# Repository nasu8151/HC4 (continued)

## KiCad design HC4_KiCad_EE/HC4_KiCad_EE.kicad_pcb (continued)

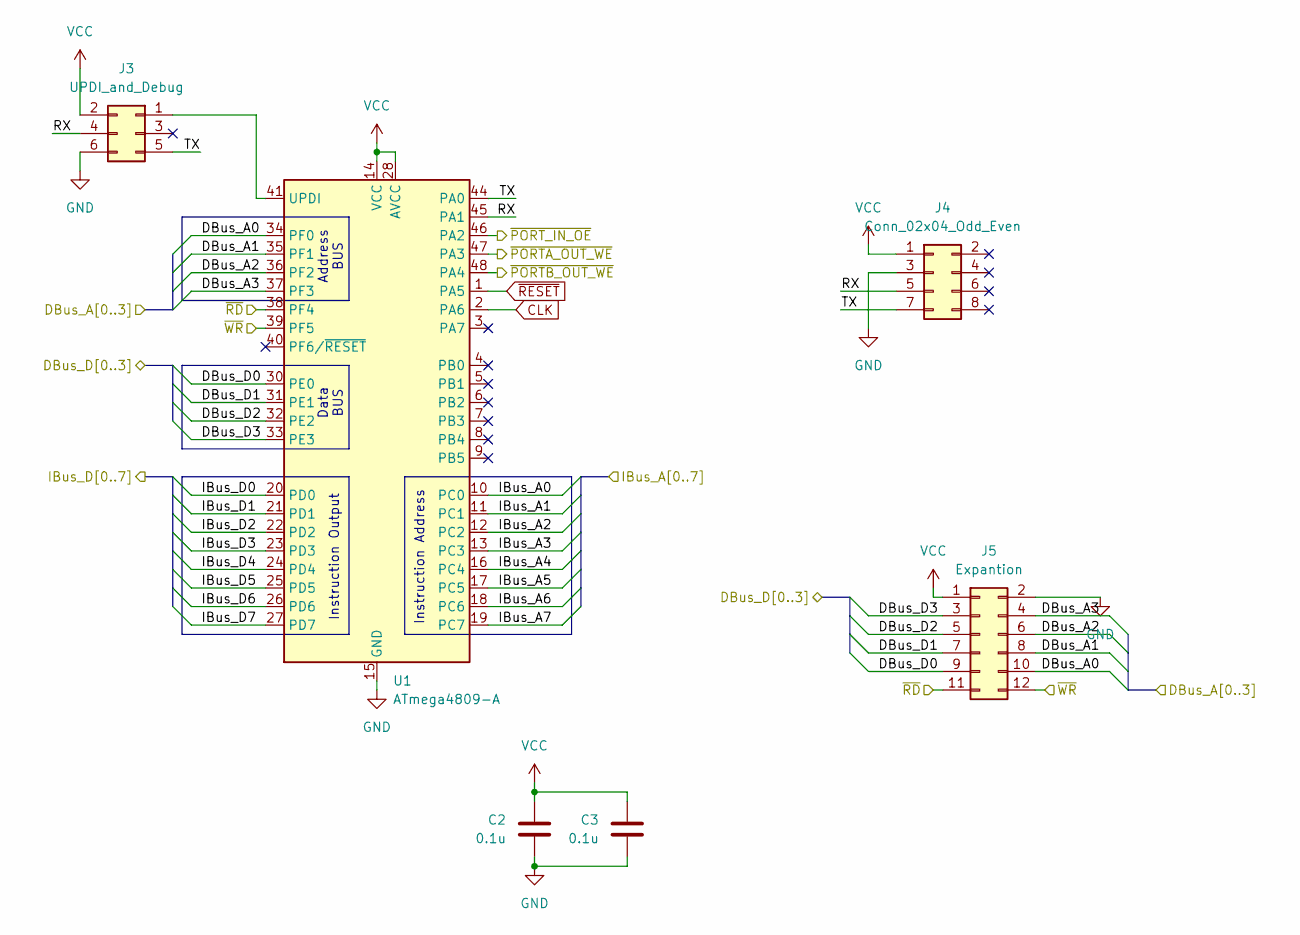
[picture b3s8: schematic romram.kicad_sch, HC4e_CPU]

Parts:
C2, C3: 0.1u; C_0603_1608Metric; LCSC PN C14663
J3: UPDI_and_Debug; PinHeader_2x03_P2.54mm_Vertical
J4: Conn_02x04_Odd_Even; PinHeader_2x04_P2.54mm_Vertical
J5: Expantion; PinHeader_2x06_P2.54mm_Vertical
U1: ATmega4809-A; TQFP-48_7x7mm_P0.5mm; LCSC PN C1340574

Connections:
/ALU/ALU_OUT0: J5.9, U1.30 (PE0); also elsewhere on the board
/ALU/ALU_OUT1: J5.7, U1.31 (PE1); also elsewhere on the board
/ALU/ALU_OUT2: J5.5, U1.32 (PE2); also elsewhere on the board
/ALU/ALU_OUT3: J5.3, U1.33 (PE3); also elsewhere on the board
/ALU/Instruction_4: U1.24 (PD4); also elsewhere on the board
/ALU/Instruction_5: U1.25 (PD5); also elsewhere on the board
/ALU/Instruction_6: U1.26 (PD6); also elsewhere on the board
/ALU/Instruction_7: U1.27 (PD7); also elsewhere on the board
/Data BUS/~IN_PORT_OE: U1.46 (PA2); also elsewhere on the board
/Data BUS/~PORTA_OUT_WE: U1.47 (PA3); also elsewhere on the board
/Data BUS/~PORTB_OUT_WE: U1.48 (PA4); also elsewhere on the board
/Instruction Decoder/~RAM_RD: J5.11, U1.38 (PF4); also elsewhere on the board
/Instruction Decoder/~RAM_WR: J5.12, U1.39 (PF5); also elsewhere on the board
/Program Counter/PC_0: U1.10 (PC0); also elsewhere on the board
/Program Counter/PC_1: U1.11 (PC1); also elsewhere on the board
/Program Counter/PC_2: U1.12 (PC2); also elsewhere on the board
/Program Counter/PC_3: U1.13 (PC3); also elsewhere on the board
/Program Counter/PC_4: U1.16 (PC4); also elsewhere on the board
/Program Counter/PC_5: U1.17 (PC5); also elsewhere on the board
/Program Counter/PC_6: U1.18 (PC6); also elsewhere on the board
/Program Counter/PC_7: U1.19 (PC7); also elsewhere on the board
/ROM_RAM/RX: J3.4, J4.5, U1.45 (PA1)
/ROM_RAM/TX: J3.5, J4.7, U1.44 (PA0)
CLK: U1.2 (PA6); also elsewhere on the board
GND: C2.2, C3.2, J3.6, J4.3, J5.2, U1.15 (GND), U1.29 (GND), U1.43 (GND); also elsewhere on the board
unnamed: J3.1, U1.41 (UPDI)
VCC: C2.1, C3.1, J3.2, J4.1, J5.1, U1.14 (VCC), U1.28 (AVCC), U1.42 (VCC); also elsewhere on the board
~RESET: U1.1 (PA5); also elsewhere on the board

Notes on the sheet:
Data BUS
Instruction Address
Instruction Output
Address BUS

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
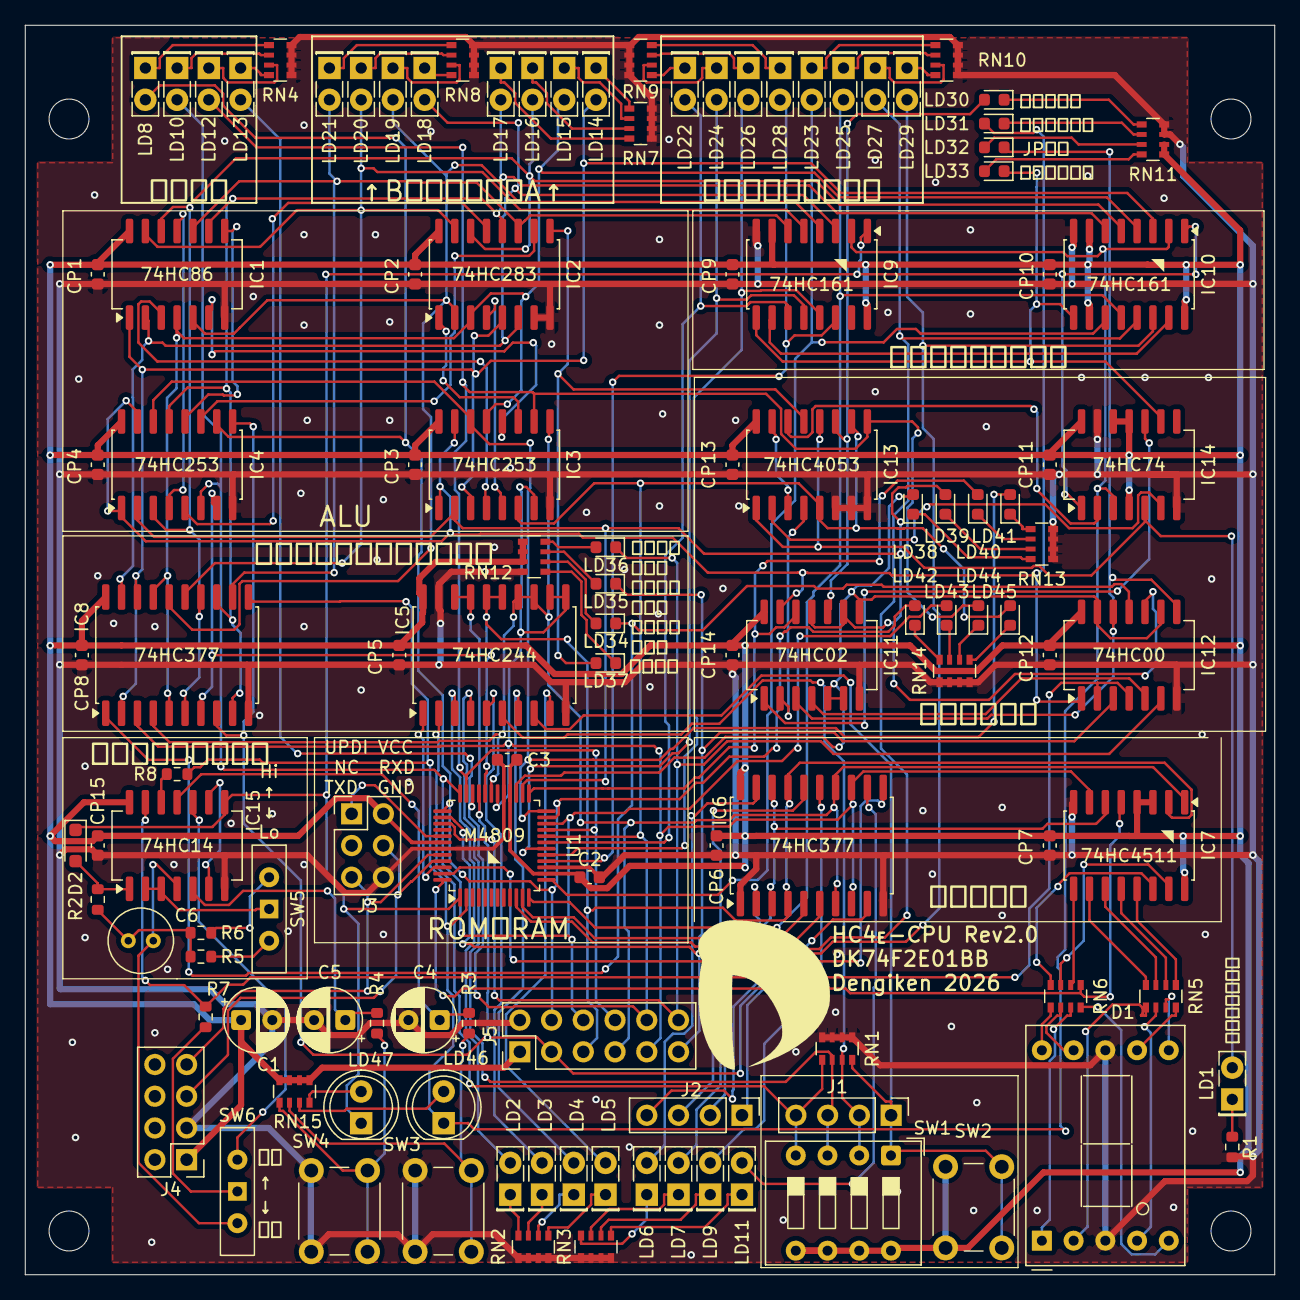
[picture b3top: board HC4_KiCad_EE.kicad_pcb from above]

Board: 2 copper layers, 100.0 x 100.0 mm, 124 parts (0 on the bottom side), 155 nets.

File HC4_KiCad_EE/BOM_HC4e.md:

| Reference    | Value               | Qty | Remarks                            |
|--------------|---------------------|-----|------------------------------------|
| C1           | 100u                | 1   |                                    |
| C2,C3,CP1-15 | 0.1u                | 17  | SMT 1608                           |
| C4,C5        | 10u                 | 2   |                                    |
| C6           | 1u                  | 1   | Use unipolar type                  |
| D1           | 7-Segment           | 1   | C-551SRD or equipment              |
| D2           | Schottky            | 1   | Switching diode in SOD-323 package |
| IC1,IC12     | 74HC00              | 2   | Use SOP package (D or *F)          |
| IC2          | 74HC283             | 1   | Use SOP package (D or *F)          |
| IC3,IC4      | 74HC253             | 2   | Use SOP package (D or *F)          |
| IC5          | 74HC244             | 1   | Use TSSOP package (PW)             |
| IC6,IC8      | 74HC377             | 2   | Use TSSOP package (PW)             |
| IC7          | 74HC4511            | 1   | Use SOP package (D or *F)          |
| IC9,IC10     | 74HC161             | 2   | Use SOP package (D or *F)          |
| IC11         | 74HC02              | 1   | Use SOP package (D or *F)          |
| IC13         | 74HC4053            | 1   | Use SOP package (D or *F)          |
| IC14         | 74HC74              | 1   | Use SOP package (D or *F)          |
| IC15         | 74HC14              | 1   | Use SOP package (D or *F)          |
| J1,J2        | Port                | 2   | Pinsocket_1x4                      |
| J3           | UPDI_and_Debug      | 1   | Pinheader_2x3                      |
| J4           | Conn_02x04_Odd_Even | 1   | USB-UART                           |
| J5           | Expantion           | 1   | Pinheader_2x5                      |
| LD1-29       | LED                 | 29  | 2x5mm Rectangler                   |
| LD30-45      | Chip                | 16  | SMT 1608                           |
| LD46         | CLK                 | 1   | D5mm, Yellow                       |
| LD47         | RESET               | 1   | D5mm, Red                          |
| R1           | 1k                  | 1   | SMT 1608                           |
| R2           | 10k                 | 1   | SMT 1608                           |
| R3           | 100k                | 1   | SMT 1608                           |
| R4           | 390k                | 1   | SMT 1608                           |
| R5           | 390                 | 1   | SMT 1608                           |
| R6,R7        | 100                 | 2   | SMT 1608                           |
| RN1          | 10k                 | 1   | Resistor array SMT 3216            |
| RN2-15       | 1k                  | 14  | Resistor array SMT 3216            |
| SW1          | SW_DIP_x04          | 1   |                                    |
| SW2,SW3,SW4  | SW_Push             | 3   |                                    |
| SW5,SW6      | SW_SPDT             | 2   |                                    |
| U1           | ATmega4809-AU       | 1   | or AVR32DB48                       |

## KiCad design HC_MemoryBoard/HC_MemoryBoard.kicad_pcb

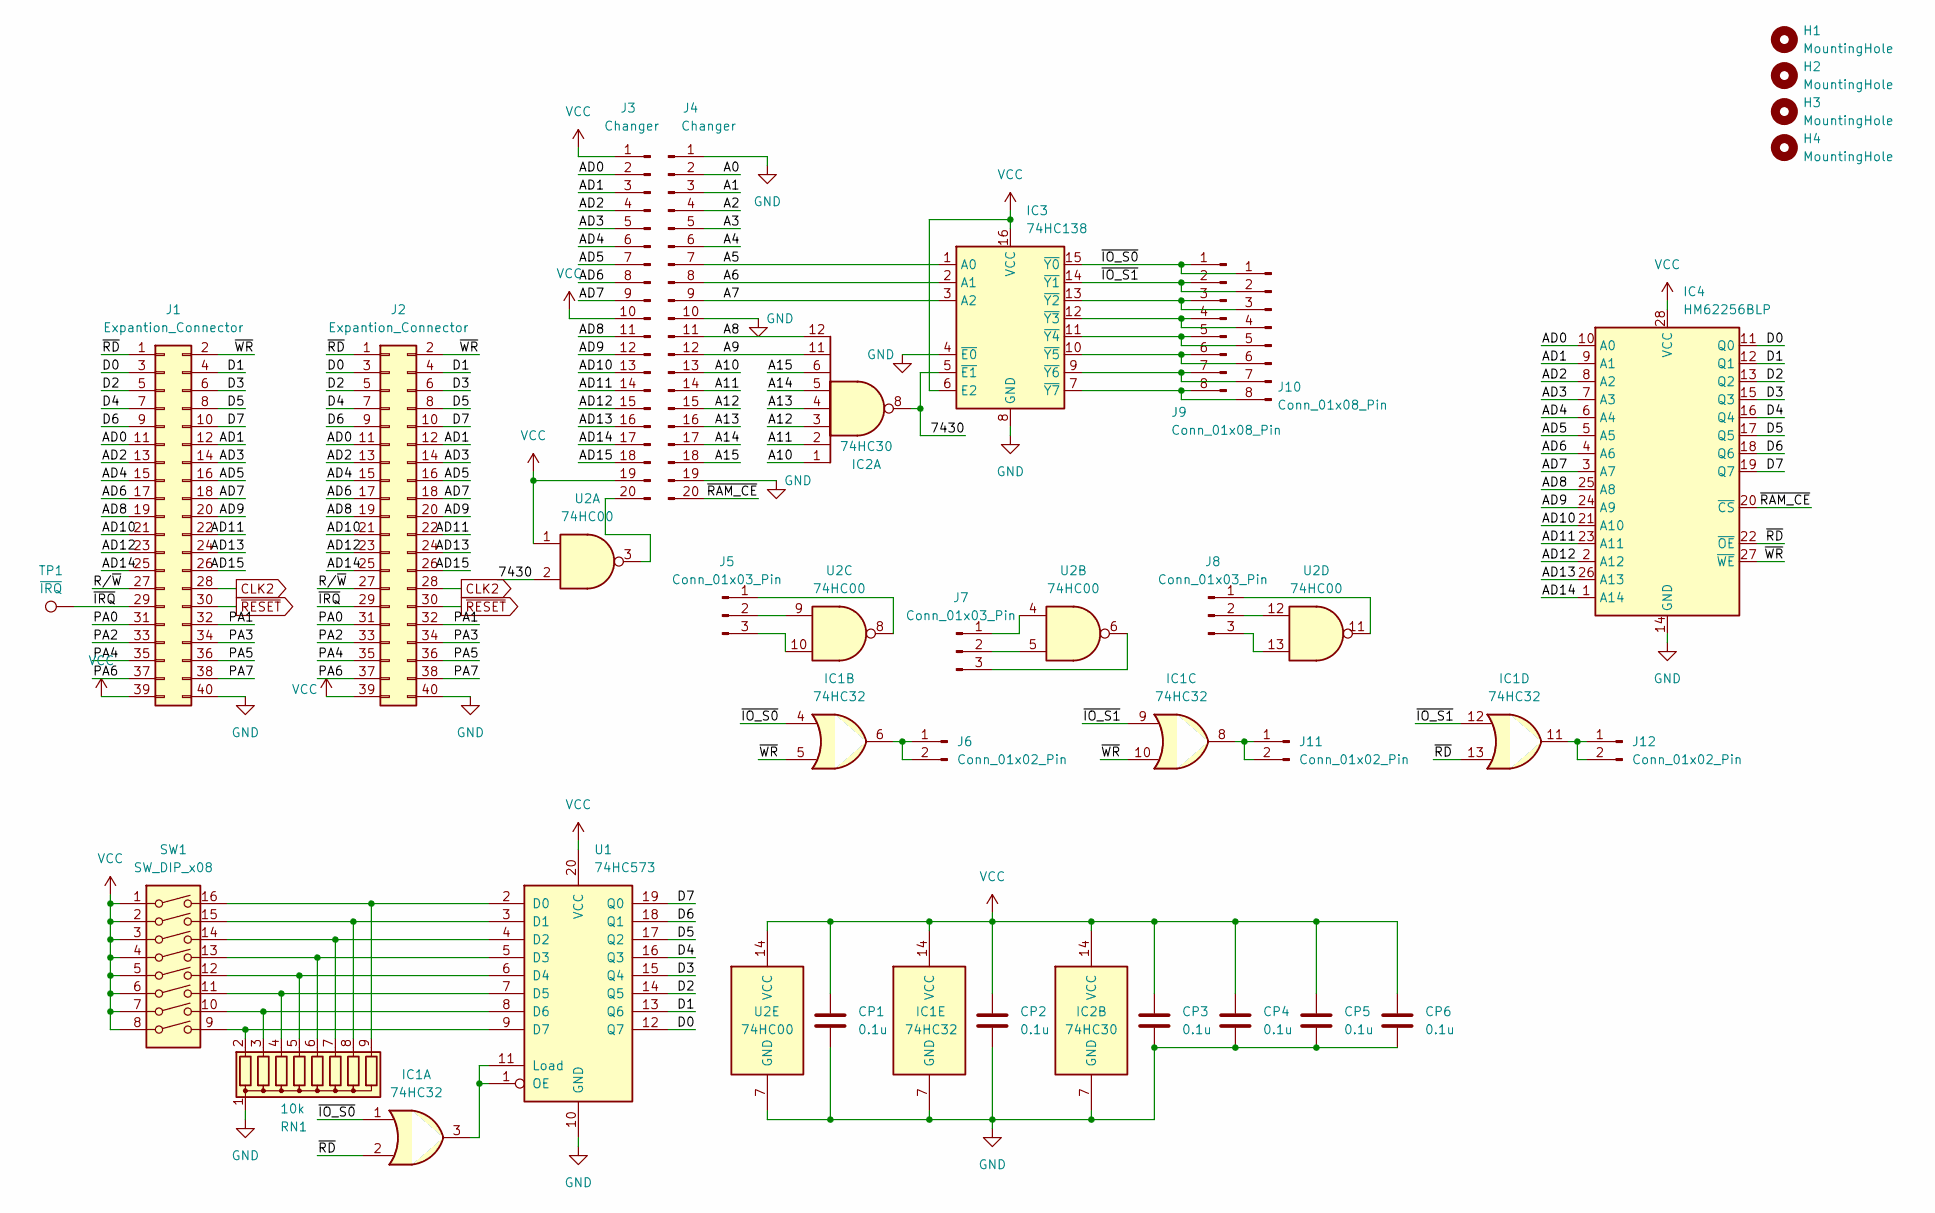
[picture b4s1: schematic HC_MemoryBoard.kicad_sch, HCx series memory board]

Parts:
CP1, CP2, CP3, CP4, CP5, CP6: 0.1u; C_Disc_D3.0mm_W1.6mm_P2.50mm
H1, H2, H3, H4: MountingHole; MountingHole_3.2mm_M3
IC1: 74HC32; DIP-14_W7.62mm
IC2: 74HC30; DIP-14_W7.62mm
IC3: 74HC138; DIP-16_W7.62mm
IC4: HM62256BLP; DIP-28_W15.24mm
J1, J2: Expantion_Connector; PinHeader_2x20_P2.54mm_Vertical
J3, J4: Changer; PinSocket_1x20_P2.54mm_Vertical
J5, J7, J8: Conn_01x03_Pin; PinSocket_1x03_P2.54mm_Vertical
J6, J11, J12: Conn_01x02_Pin; PinHeader_1x02_P2.54mm_Vertical
J9, J10: Conn_01x08_Pin; PinHeader_1x08_P2.54mm_Vertical
RN1: 10k; R_Array_SIP9
SW1: SW_DIP_x08; SW_DIP_SPSTx08_Slide_9.78x22.5mm_W7.62mm_P2.54mm
TP1: ~{IRQ}; PinHeader_1x01_P2.54mm_Vertical
U1: 74HC573; DIP-20_W7.62mm
U2: 74HC00; DIP-14_W7.62mm

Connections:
/7430: IC2.8, IC3.5 (~E1), U2.2
/A0: J4.2
/A1: J4.3
/A2: J4.4
/A3: J4.5
/A4: J4.6
/A5: IC3.1 (A0), J4.7
/A6: IC3.2 (A1), J4.8
/A7: IC3.3 (A2), J4.9
/A8: IC2.12, J4.11
/A9: IC2.11, J4.12
/A10: IC2.1, J4.13
/A11: IC2.2, J4.14
/A12: IC2.3, J4.15
/A13: IC2.4, J4.16
/A14: IC2.5, J4.17
/A15: IC2.6, J4.18
/AD0: IC4.10 (A0), J1.11, J2.11, J3.2
/AD1: IC4.9 (A1), J1.12, J2.12, J3.3
/AD2: IC4.8 (A2), J1.13, J2.13, J3.4
/AD3: IC4.7 (A3), J1.14, J2.14, J3.5
/AD4: IC4.6 (A4), J1.15, J2.15, J3.6
/AD5: IC4.5 (A5), J1.16, J2.16, J3.7
/AD6: IC4.4 (A6), J1.17, J2.17, J3.8
/AD7: IC4.3 (A7), J1.18, J2.18, J3.9
/AD8: IC4.25 (A8), J1.19, J2.19, J3.11
/AD9: IC4.24 (A9), J1.20, J2.20, J3.12
/AD10: IC4.21 (A10), J1.21, J2.21, J3.13
/AD11: IC4.23 (A11), J1.22, J2.22, J3.14
/AD12: IC4.2 (A12), J1.23, J2.23, J3.15
/AD13: IC4.26 (A13), J1.24, J2.24, J3.16
/AD14: IC4.1 (A14), J1.25, J2.25, J3.17
/AD15: J1.26, J2.26, J3.18
/D0: IC4.11 (Q0), J1.3, J2.3, U1.12 (Q7)
/D1: IC4.12 (Q1), J1.4, J2.4, U1.13 (Q6)
/D2: IC4.13 (Q2), J1.5, J2.5, U1.14 (Q5)
/D3: IC4.15 (Q3), J1.6, J2.6, U1.15 (Q4)
/D4: IC4.16 (Q4), J1.7, J2.7, U1.16 (Q3)
/D5: IC4.17 (Q5), J1.8, J2.8, U1.17 (Q2)
/D6: IC4.18 (Q6), J1.9, J2.9, U1.18 (Q1)
/D7: IC4.19 (Q7), J1.10, J2.10, U1.19 (Q0)
/PA0: J1.31, J2.31
/PA1: J1.32, J2.32
/PA2: J1.33, J2.33
/PA3: J1.34, J2.34
/PA4: J1.35, J2.35
/PA5: J1.36, J2.36
/PA6: J1.37, J2.37
/PA7: J1.38, J2.38
/R/~W: J1.27, J2.27
/~IO_S0: IC1.1, IC1.4, IC3.15 (~Y0), J9.1, J10.1
/~IO_S1: IC1.9, IC1.12, IC3.14 (~Y1), J9.2, J10.2
/~IRQ: J1.29, J2.29, TP1.1
/~RAM_CE: IC4.20 (~CS), J4.20
/~RD: IC1.2, IC1.13, IC4.22 (~OE), J1.1, J2.1
/~WR: IC1.5, IC1.10, IC4.27 (~WE), J1.2, J2.2
CLK2: J1.28, J2.28
GND: CP1.2, CP2.2, CP3.2, CP4.2, CP5.2, CP6.2, IC1.7 (GND), IC2.7 (GND), IC3.4 (~E0), IC3.8 (GND), IC4.14 (GND), J1.40, J2.40, J4.1, J4.10, J4.19, RN1.1 (common), U1.10 (GND), U2.7 (GND)
unnamed: IC3.13 (~Y2), J9.3, J10.3
unnamed: IC3.12 (~Y3), J9.4, J10.4
unnamed: IC3.11 (~Y4), J9.5, J10.5
unnamed: IC3.10 (~Y5), J9.6, J10.6
unnamed: IC3.9 (~Y6), J9.7, J10.7
unnamed: IC3.7 (~Y7), J9.8, J10.8
unnamed: J3.20, U2.3
unnamed: J5.1, U2.8
unnamed: J5.2, U2.9
unnamed: J5.3, U2.10
unnamed: IC1.6, J6.1, J6.2
unnamed: J7.1, U2.4
unnamed: J7.2, U2.5
unnamed: J7.3, U2.6
unnamed: J8.1, U2.11
unnamed: J8.2, U2.12
unnamed: J8.3, U2.13
unnamed: IC1.8, J11.1, J11.2
unnamed: IC1.11, J12.1, J12.2
unnamed: RN1.2 (R1), SW1.9, U1.9 (D7)
unnamed: RN1.3 (R2), SW1.10, U1.8 (D6)
unnamed: RN1.4 (R3), SW1.11, U1.7 (D5)
unnamed: RN1.5 (R4), SW1.12, U1.6 (D4)
unnamed: RN1.6 (R5), SW1.13, U1.5 (D3)
unnamed: RN1.7 (R6), SW1.14, U1.4 (D2)
unnamed: RN1.8 (R7), SW1.15, U1.3 (D1)
unnamed: RN1.9 (R8), SW1.16, U1.2 (D0)
unnamed: IC1.3, U1.1 (OE), U1.11 (Load)
VCC: CP1.1, CP2.1, CP3.1, CP4.1, CP5.1, CP6.1, IC1.14 (VCC), IC2.14 (VCC), IC3.6 (E2), IC3.16 (VCC), IC4.28 (VCC), J1.39, J2.39, J3.1, J3.10, J3.19, SW1.1, SW1.2, SW1.3, SW1.4, SW1.5, SW1.6, SW1.7, SW1.8, U1.20 (VCC), U2.1, U2.14 (VCC)
~RESET: J1.30, J2.30

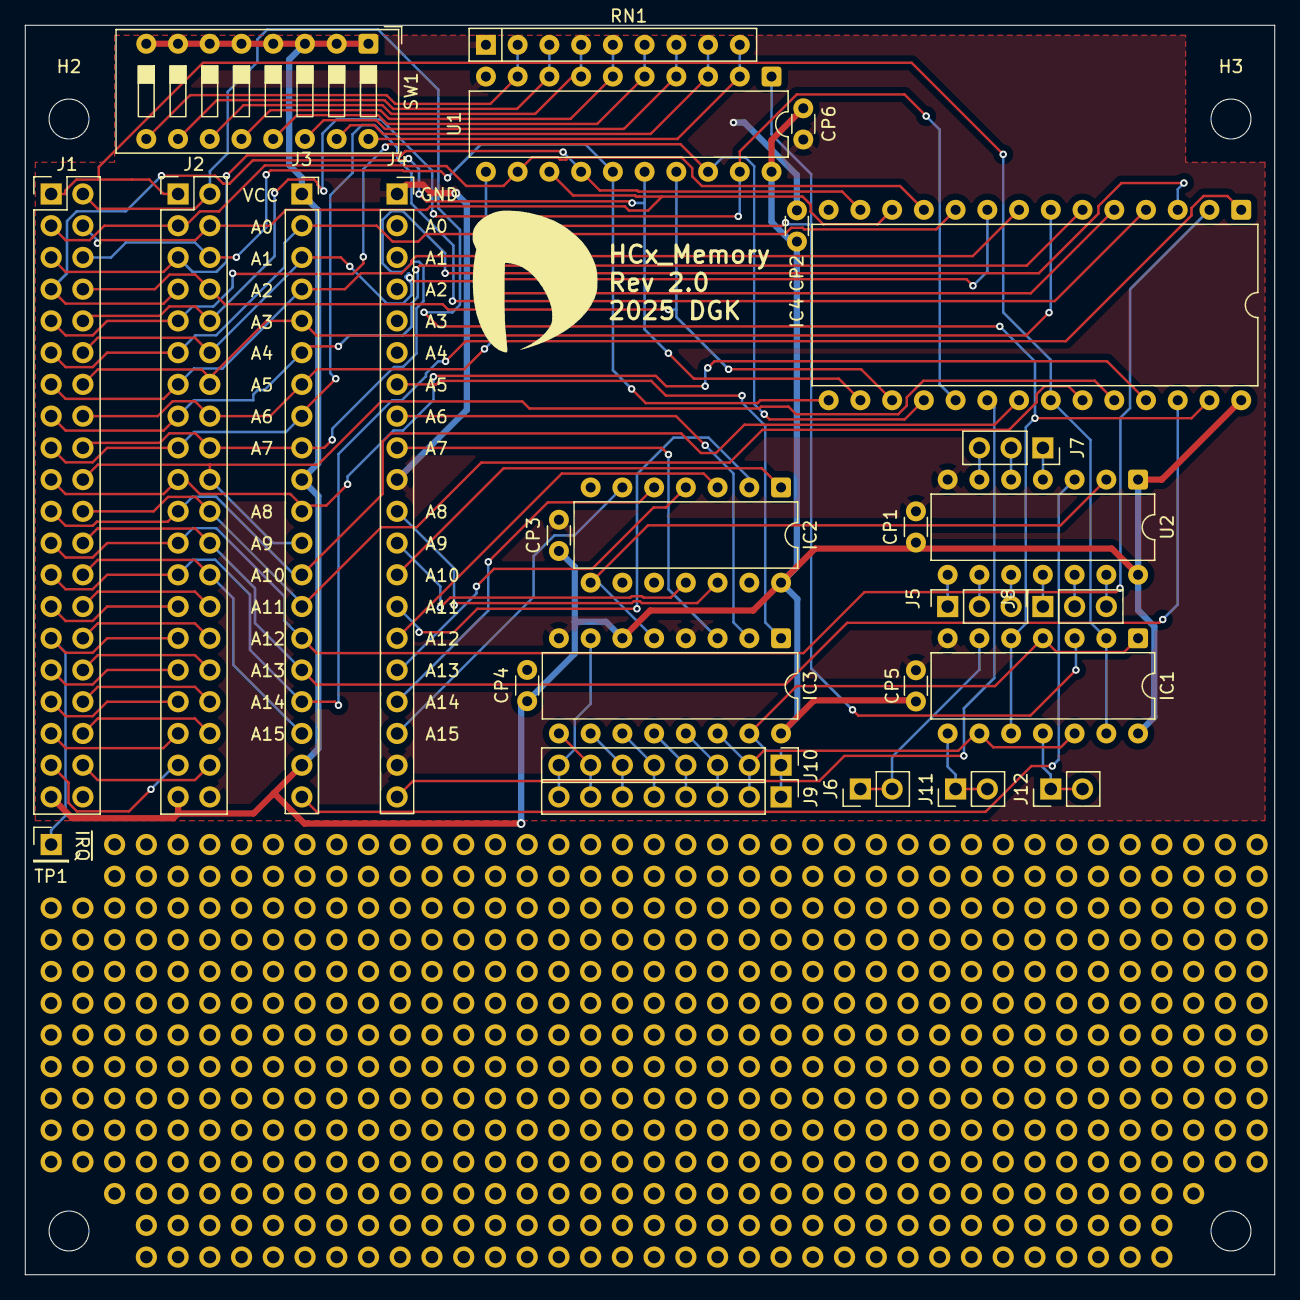
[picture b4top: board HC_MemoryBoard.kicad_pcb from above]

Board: 2 copper layers, 100.0 x 100.0 mm, 31 parts (0 on the bottom side), 83 nets.

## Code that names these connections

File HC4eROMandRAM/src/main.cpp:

#include <Arduino.h>

/*
 * HC4eROMandRAM.ino ── 128 B ROM (EEPROM) + 16×4‑bit RAM/I/O “三役” 完全版
 *   2025‑07‑18   Intel‑HEX 行毎即書込み版 + 小文字 l,r コマンド
 *   2025‑07‑18b  CR を無視し LF で行確定（空行 ERR 解消）
 *
 * ─── 概要 ──────────────────────────────────
 *  UART コマンド (115200‑8N1, LF)
 *    L / l  : Intel‑HEX ローダ  (1 行ずつ即 EEPROM 書込み)
 *    R / r  : 4‑bit RAM ダンプ   (16 word, comma separated)
 *
 *  内蔵 EEPROM 0‑255 を ROM 領域として読み出し、
 *  外付け 4‑bit RAM を PC2‑5, PE0‑3, PF0‑1 で制御。
 *────────────────────────────────────────────*/

#include <avr/io.h>

#include "disasm.h"
#include "hex.h"

/************* 定数 ******************************/
#define BAUD_RATE 115200

/************* Port/F ビット定義 ******************/
#define PF_nRD_bp 4
#define PF_nWR_bp 5

#define PIN_nRD PIN_PF4
#define PIN_nWR PIN_PF5

#define PA_AIN_bp 2
#define PA_AOUT_bp 3
#define PA_BOUT_bp 4

#define PIN_nPORT_OE  PIN_PA2
#define PIN_nPORTA_WE PIN_PA3
#define PIN_nPORTB_WE PIN_PA4

#define PIN_CLK PIN_PA6
#define PIN_RST PIN_PA5

/************* 4‑bit RAM/I‑O *********************/
volatile uint8_t ram4[16] = { 0 }; /* 4‑bit ×16 word */

volatile uint8_t latchedAddr = 0;
volatile uint8_t latchedData = 0;

volatile uint8_t curnWR;
volatile uint8_t curnRD;

volatile uint8_t onclkrise = 0;

// 256x8bit ROM for HC4e program
volatile uint8_t rom8[MEM_SIZE];

uint8_t ontrace = 0;

/************* 4‑bit RAM ダンプ *******************/
static void ramDump(char *args) {
  if (*args == 'h' || *args == 'H') {
    Serial.println("Usage: R");
    Serial.println(" Dumps 16x4-bit RAM contents.");
    return;
  } else if (*args == 'c' || *args == 'C') {
    for (uint8_t i = 0; i < 16; i++) {
      Serial.print(ram4[i]);
      Serial.write(',');
    }
    uint8_t pc = VPORTC.IN;
    Serial.print(pc);
    Serial.print(',');
    Serial.println(rom8[pc]);
  } else {
    Serial.println("r0  r1  r2  r3  r4  r5  r6  r7  r8  r9  r10 r11 r12 r13 r14 r15");
    for (uint8_t i = 0; i < 16; i++) {
      if (ram4[i] < 10) Serial.write(' ');
      Serial.print(ram4[i]);
      if (i == 15) {
        Serial.println();
        break;
      } else {
        Serial.write(',');
      }
      Serial.write(' ');
    }
    uint8_t pc = VPORTC.IN;
    Serial.print("PC=");
    Serial.print(pc);
    Serial.print(", Inst=");
    Serial.print(rom8[pc], HEX);
    Serial.print(" (");
    Serial.print(disasm(rom8[pc]));
    Serial.println(")");
  }
}

static void trace() {
  if (Serial.available()) {
    char c = Serial.read();
    if (c == 0x03) { // Ctrl-C
      ontrace = 0;
      Serial.print("Trace stopped.\n> ");
      return;
    }
  }
  if (onclkrise) {
    onclkrise = 0;
    ramDump("c");
  }
}

static void startTrace() {
  ontrace = 1;
  Serial.println("Trace started. (Ctrl-C to stop)");
}

static void help() {
  Serial.println("r or R : Read HC4e RAM data");
  Serial.println("l or L : Load to HC4e ROM");
  Serial.println("t or T : Trace execution (Ctrl-C to stop)");
  Serial.println("         *make sure HC4e CPU is running and in low clock mode.");
  Serial.println("h or H : Help");
}

/************* UART コマンド受付 ******************/
static void programUART() {
  static char buf[8];
  static uint8_t idx = 0;

  while (Serial.available()) {
    char c = Serial.read();
    if (0x20 <= c) Serial.write(c);
    if (c == '\r') continue; /* CR 無視 */
    if (c == '\n') {
      Serial.write('\n');
      if (idx == 0) { 
        Serial.print("> "); 
        continue; 
      } /* 連続改行は無視 */
      buf[idx] = '\0';
      char cmd = buf[0];
      char *args = &buf[1];
      while (*args == ' ') args++; /* スペーススキップ */
      if (cmd == 'l' || cmd == 'L') intelhexLoad(args);
      else if (cmd == 'r' || cmd == 'R') ramDump(args);
      else if (cmd == 't' || cmd == 'T') startTrace();
      else if (cmd == 'h' || cmd == 'H') help();
      else Serial.println("Unknown command. type 'h' for help.");
      idx = 0; /* バッファクリア */
      if (ontrace == 0) Serial.print("> ");

    } else if (idx < sizeof(buf) - 1) {
      buf[idx++] = c;
    }
  }
}

/************* Arduino 標準関数 *******************/
void setup() {
  Serial.begin(BAUD_RATE);

  /* --- RAM/I/O バス設定 --- */
  PORTF.DIR &= ~0x0F;
  PORTF.DIR &= ~((1 << PF_nRD_bp) | (1 << PF_nWR_bp));
  PORTE.DIR &= ~0x0F;  // PE0‑3 データ Hi‑Z
  PORTE.OUT &= ~0x0F;

  PORTF.DIR &= ~((1 << PF_nRD_bp) | (1 << PF_nWR_bp));
  PORTA.DIR |= (1 << PA_AIN_bp) | (1 << PA_AOUT_bp) | (1 << PA_BOUT_bp);
  VPORTA.OUT |= (1 << PA_AIN_bp) | (1 << PA_AOUT_bp) | (1 << PA_BOUT_bp);  // disable (負論理)

  /* --- PA/PD (ROM 出力) --- */
  PORTC.DIR = 0x00;  // PC 入力 (アドレス)
  PORTD.DIR = 0xFF;  // PD 出力 (データ)
  VPORTD.OUT = 0x00;

  // TCB0.CTRLB = TCB_CNTMODE_INT_gc; // 割り込みモード
  // TCB0.INTCTRL = TCB_CAPT_bm;  // 周期的割り込み許可
  // TCB0.CCMP = (F_CPU / 1000);  // 3kHz
  // TCB0.CTRLA = TCB_CLKSEL_CLKDIV1_gc | TCB_ENABLE_bm;

  PORTA.PIN6CTRL = PORT_ISC_RISING_gc;  // clk 立ち上がり
  PORTF.PIN4CTRL = PORT_ISC_FALLING_gc; // nRD 立ち下がり
  PORTF.PIN5CTRL = PORT_ISC_FALLING_gc; // nWR 立ち下がり

  Serial.println("\nHC4e ROM/RAM Monitor");
  Serial.print("> ");

  for (uint16_t i = 0; i < MEM_SIZE; i++) { // ROM配列の初期化
    rom8[i] = EEPROM.read(i);
  }

  while (1) {
    // ---- RD処理（そのままでOK）

    if (digitalReadFast(PIN_RST) == 0) { //リセット時にもROM読み出し
      uint8_t ad = VPORTC.IN;
      VPORTD.OUT = rom8[ad];
    }
    if (ontrace == 0) {
      programUART();
    } else {
      trace();
    }
    delay(10); /* CPU負荷軽減 */
  }
}


void loop() {

}

// クロック立ち上がりエッジ割り込み
// ROM読み込み, PORTA制御, RAM書込み
ISR(PORTA_PORT_vect) {
  VPORTA.OUT |= PIN4_bm | PIN2_bm | PIN3_bm; // nPORT_OE, nPORTA_WE, nPORTB_WE デアサート
  PORTA.INTFLAGS = PIN6_bm;
  VPORTE.DIR &= ~0x0F;
  onclkrise = 1;
  uint8_t a = VPORTC.IN;
  VPORTD.OUT = rom8[a];
  // VPORTD.OUT = EEPROM.read(a);
  if (curnWR == 0) {   // curnWR は割り込み直前のnWRの状態なので...
    ram4[latchedAddr] = latchedData;
    return;
  }
  return;
}

// nRD/nWR立ち下がりエッジ
ISR(PORTF_PORT_vect) {
  curnWR = digitalReadFast(PIN_nWR);
  curnRD = digitalReadFast(PIN_nRD);
  VPORTE.DIR &= ~0x0F;
  latchedAddr = VPORTF.IN & 0x0F;
  latchedData = VPORTE.IN & 0x0F;
  // /WRがLOWの間に常にラッチ（番地ズレ対策）
  if (curnWR == 0) {
    VPORTF.INTFLAGS = (1 << PF_nWR_bp);
    switch (latchedAddr) {
    case 0x0E:
      VPORTA.OUT &= ~(1 << PA_AOUT_bp);  // nPORTA_WE アサート
      break;
    case 0x0F:
      VPORTA.OUT &= ~(1 << PA_BOUT_bp);  // nPORTB_WE アサート
      break;
    default:
      break;
    }
  }
  if (curnRD == 0) { // nRDがアサートされていたら
    VPORTF.INTFLAGS = (1 << PF_nRD_bp);
    if (latchedAddr == 0x0E) {
      VPORTE.DIR &= ~0x0F;  // バスを開放
      VPORTA.OUT &= ~(1 << PA_AIN_bp);  // nPORT_OE アサート
    } else {
      VPORTE.DIR |= 0x0F;
      VPORTE.OUT = ram4[latchedAddr];
    }
  }
}

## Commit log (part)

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2025-01-15 HC8-16から一部移植
2025-01-15 modified: README.md
2025-01-16 ブロック図の更新
2025-01-16 rom and ram
2025-01-17 My English is very bad. So I cant write as you can read.
2025-01-18 レジスタを4bit,カウンタを12bit,ramを少し変更
2025-01-19 コンパイル'は'通った。動くとは決して言ってない。ついでに誤字直して、いらんファイル消した。
2025-01-20 一旦コミット
2025-01-20 テストプログラム
2025-01-25 add kicad files
2025-01-26 JP,NP指定部を修正
2025-01-27 add `jnc` and `jnz` instructions
2025-01-27 errata collect
2025-01-27 細かいバグを修正
2025-01-27 マージで発生したバグを修正
2025-01-29 level_Aがリセットされるように変更、```JP```系のニーモニック変更
2025-02-03 進捗コミット
2025-02-07 命令レジスタを削除。
2025-02-08 進捗コミット2
2025-02-09 I'm tired. あとは任せた 頑張りたまえ
2025-02-12 74HCのフットプリントの指定および基板の更新
2025-02-13 回路図の修正
2025-02-13 ALU基板の製作途中
2025-02-13 フットプリントの割り当て修正
2025-02-13 ALU単体の配線完了(芸術点Up)
2025-02-14 Adress Busを若干配線
2025-02-15 ファイル整理、BOM作成
2025-02-15 Adress Bus完成(芸術点Up)
2025-02-15 DataBus製作途中
2025-02-16 BOMを詳細に
2025-02-17 電源周りが詰みそう
2025-02-17 更地になった。
2025-02-17 ICの配置を再検討
2025-02-17 ICを再配置
2025-02-17 再配置ほぼ完了
2025-02-20 StackLEDつけた
2025-02-20 とりあえずIC配置確定
2025-02-21 電源配線ほぼ完了
2025-02-21 ALUとスタックの配線完了
2025-02-21 上半分の配線だいたい終わった
2025-02-22 基盤完成
2025-02-22 ガーバーとドリルを出力
2025-02-22 基板手直し完成
2025-02-23 またも手直し
2025-02-23 ガーバーとドリルを修正
2025-02-23 謎の衝突が発生したのでガーバーを修正
2025-02-23 フォルダはガラクタ置き場ではありません。以後気を付けるように。
2025-03-09 メモリーを外に出した ガーバーを修正した
2025-03-12 ドキュメンテーションをちょっと充実
2025-03-16 HC8動いたかも
2025-03-18 create cargo project #2
    コマンドライン引数を読み取るプログラムを書いておいた
2025-03-18 ファイルを一行ごとに読み込むことに成功 #2
2025-03-20 add package regex #3
2025-03-20 デバック用のアセンブリファイルを作成 #4
2025-03-20 仕様書から命令と構文解釈の正規表現を静的宣言 #3
2025-03-20 正規表現のインデックスが命令のopcになっていると便利なため、配列の順番を組み替える関数を作成 #3
    関数で組み替えた配列のインデックスが命令のはじめ4bitとなるようにした。
2025-03-20 アセンブリの構文解釈に必要なものを読み込む #4
2025-03-20 一通り読むためのプログラムを記述（コンパイルエラー） #4
2025-03-20 おまじない #4
2025-03-20 命令文の正規表現をわかりやすく書き直し #4
2025-03-20 空白行を無視 #4
2025-03-20 コンパイルエラー修正 #4
2025-03-20 メモリ番地を数字として解釈できるように #4
2025-03-20 エラーの感知を修正 #4
2025-03-20 ログを整理 #4
2025-03-20 JPの台に引数処理のコードを適切に修正 #4
2025-03-20 コメントテスト用にテストようのアセンブリファイルにコメントを追加 #4
2025-03-20 コメントに対応させる #4
2025-03-20 JP命令対応をさせた #4
2025-03-20 Create specification of ASSEMBLER syntax
2025-03-20 必要なクレートを追加 #4
2025-03-20 コマンドライン引数からオプションを読み取れるように #4
    -o 出力ファイルパス
    -h --help ヘルプ
2025-03-20 ファイルに書き出し成功 #4
2025-03-20 不必要な標準出力を削除 #4
2025-03-20 構文エラー修正 #4
2025-03-20 ターミナルの文字を色付け #4
2025-03-20 デバックで生成された hex ファイル #8
2025-03-20 ドキュメント類の充実、verilogの小修正
2025-03-21 小文字の動作テストのために小文字で書かれたアセンブリファイルを作成 #12
2025-03-21 正規表現を小文字にして、ファイルを読んだあとに読んだ内容を小文字にして変換して扱うことで対応 #12
2025-03-21 動作確認 => 成功 #12
2025-03-21 コメントアウトの記号変更に伴うデバック用のテストアセンブリのコメントアウト記号の変更 #14
2025-03-21 コメントの文字を // から ; へ変更 #14
2025-03-22 2進数, 16進数, 10進数の表現のデバック用にアセンブリを修正 #11
2025-03-22 2, 16, 10 進数表記に対応するため、JP以外の命令記述の第二引数に英数字とアンダーバーを受け取ようにする。 #11
2025-03-22 謝ったエラー行が表示される問題を修正 #11
2025-03-22 コメント追加 #11
2025-03-22 2, 16, 10 進数の文字列からuintに解釈するための関数を宣言 #11
2025-03-22 デバック用にエラーの種類を標準出力するように設定。 #11
2025-03-22 use 忘れ #11
2025-03-22 命令の第二引数の種類が同一物をまとめた配列を作成（使う機会があるかも） #11
2025-03-22 2, 16, 10 進数を解釈して適応できるようにコードを追加 #11
2025-03-22 2, 10, 16 進数の解釈が成功していることの確認 #11
2025-03-22 エラーメッセージを改善
2025-03-22 opc を4bit で表せる数の範囲かどうかの確認を追加 #11
2025-03-22 命令記述の種類を並べた配列を整理 #16
2025-03-22 アセンブリのエラーのenum型を作成 #16
2025-03-22 アセンブリ自体の構文定義を適切に書き直し #16
2025-03-22 アセンブリ時のエラーの種類をenumで置き換え。 #16
2025-03-22 余分な空白行を削除 #16
2025-03-22 分かりやすくコメントを書く
2025-03-22 美しいフォーマットでエラーを出力できるようにした。 #16
2025-03-22 エラー表示の英語のスペルミスを修正 #16
2025-03-24 ドキュメントの修正、サンプルファイルの追加
2025-03-28 表記を実際の信号に合わせた 表記をややわかりやすくした
2025-03-31 回路の改良 試験は明日やる
2025-04-01 命令フェッチをパイプライン化
2025-04-01 メモリを外付けに
2025-04-03 メモリ容量増加
2025-04-03 フットプリントをSOPに変更
2025-04-04 Spiceのファイルを追加
2025-04-08 さようなら、爺さん
2025-04-08 pseudo-pipeline
2025-04-08 バス解放機能を追加
2025-04-09 Added output port for blink
2025-04-11 部品配置完了
2025-04-12 配線完了とみられる
2025-04-12 BOM更新
2025-04-12 ガーバーファイルを出力
2025-04-13 基板のイメージ画像出力、ラーメンタイマー修正
2025-04-19 リビジョン番号いれた
2025-04-19 Gerber
2025-04-20 メモリーボード
2025-05-03 分岐遅延スロット
2025-05-03 サブルーチンコール
2025-05-05 LS, JL, LP命令(HC8用)を追加
2025-05-05 未定義フラグに反応しない問題を修正
2025-05-05 intelhex test
2025-05-06 ミスを修正
2025-05-06 ガーバーがガバガバだったのを修正
2025-05-07 なんか変わってた
2025-05-12 Checked
2025-05-26 add HC4e files
2025-05-26 仕様決め
2025-05-28 一部を整地
2025-05-30 コミット忘れてたてへ
2025-06-10 4809を別シートに、ほか
2025-06-14 完成かも～
2025-06-14 ドキュメントを少々
2025-06-14 Carry_ENを論理反転、回路図の修正
2025-06-15 技術的負債を消した
2025-06-16 PortBを4511に、フットプリントの割り付け開始
2025-06-19 何故かA3になってたのをA4に変更
2025-06-20 チップ集合抵抗に変更、基板作成開始
2025-07-05 配線進捗、7474を使った変な回路
2025-07-11 ROMのUART書き込み機構まで完成
2025-07-12 テスト用プログラム
2025-07-12 自動配線前バックアップ
2025-07-13 LEDの抵抗を入れ替え
2025-07-14 HC4eのverilogファイル追加
2025-07-14 verilogを修正
2025-07-16 基板完成
2025-07-16 プログラム(多分)完成
2025-07-16 バイナリむずい
2025-07-17 ドキュメントを充実
2025-07-17 流れ図を追加
2025-07-18 Intelhexで記入できるように修正 RAM部分のフローチャートはよくわからなかったけど動いてるからヨシ!
2025-07-19 振出しに戻る
2025-07-19 入力テスト用プログラム
2025-07-19 自動配線前最終チェック
2025-07-19 自動配線できた
2025-07-21 割り込み部分の条件をWRとRDに修正
2025-07-21 RAM部分のフローチャートを個人的な解釈で修正 解釈ミスあったらIssuesかディスコで教えて
2025-07-21 RD命令部のミスを修正
2025-07-22 たぶん完成！！！！！！！
2025-07-23 電子サイコロ
2025-07-27 表面実装用にプログラムを修正
2025-07-30 少し修正
2025-07-31 label開発開始
2025-07-31 HC4eのVerilogにI/Oを追加 プログラムのI/Oの解釈ミスを修正
2025-07-31 妥協に妥協を重ね妥協を加速する あとクロックの起動が安定しないのを直した
2025-08-01 部品表リメイク
2025-08-03 Update KiCad project files and schematic components
    - Changed active layer from 0 to 5 in HC4_KiCad_EE.kicad_prl.
    - Adjusted minimum resolved spokes from 2 to 1 and updated solder mask clearance in HC4_KiCad_EE.kicad_pro.
    - Corrected resistor value from "3.9k" to "390" in clockandreset.kicad_sch.
    - Added fabrication toolkit options JSON file for project configuration.
    - Modified LED component positions in instructiondecode.kicad_sch for better alignment.
    - Created .gitignore file in production directory to exclude unnecessary files.
2025-08-03 ドキュメントをHC4eに合わせたかも
2025-08-03 AIテスト:リストファイルを出力できるように
2025-08-03 ラベルを読み込んでリストファイルに反映できるように パースはまだ
2025-08-04 ガーバー再出力
2025-08-04 ラベル検出の処理を改善し、命令部分を抽出するロジックを追加。また、エラーが発生した場合でもリストファイルを生成する処理を整理。
2025-08-18 ドキュメントを新しいアセンブラに対応
2025-08-18 マージミスった
2025-08-28 CPUの回路図を追加
2025-08-28 HC4eの回路図pdfを修正
2025-09-08 blink@100kHz
2025-09-13 LCDプログラムを作った(動いてない)
2025-09-17 LCD用のテストベンチ
2025-09-21 LCD表示成功！！！！！！！！
2025-09-23 LCDでカウンタ
2025-09-23 LED機能を追加
2025-09-28 オープニングメッセージを変更、4桁に対応
2025-10-05 ブロック図を修正、ROMエミュレータのプログラムの書式整理、高速化への準備、RAM部分の処理の見直し
2025-10-28 ソフトウェアで割り込みをエミュレート
2025-10-29 wait入れたら動いた
2025-10-31 ループ内でのRAMの読み書き処理をsetup関数に移動し、delayを750マイクロ秒に変更
2025-10-31 HC8命令セット再検討
2025-11-01 HC4e設計変更:CH340に敗北宣言、USBシリアル仕様に変更
2025-11-03 ガーバー
2025-11-04 Memboardv2.0
2025-11-11 Add files via upload
    HC4紹介スライドを追加
2025-11-12 HC4e_Rev1.2
2025-12-12 新ユーザーズマニュアル
2025-12-12 ROM制御のタイミングを変更し、RAM制御のタイミングも変更。
2025-12-17 moti
2025-12-23 RAMが動作しない問題とROMに長い命令を書き込めない問題を修正
2025-12-23 HC4モジュールの新規作成とALU機能の実装
2025-12-24 UARTコマンドの説明を更新し、ROM配列の初期化処理を追加。不要なコードを削除し、RAMダンプとヘルプ機能を強化。
2025-12-24 RAM書き込み処理を強化し、volatile修飾子を追加。RAMのアドレスとデータをラッチするための変数を定義。
2025-12-28 port to PlatformIO and add disassembler
2025-12-28 Fix image paths in README.md for consistency
    Microsoftを許してはいけない
2025-12-28 プラットフォームIOの設定を更新し、Intel-HEX形式のデータをHC4e ROMに読み込む機能を強化。RAMダンプ機能に引数を追加し、トレース機能を実装。
2025-12-28 RAM処理をTCBの割り込みで行うようにし、最適化した。もしかしたら1kHz復活いけるかも
2026-01-10 MOSFETを回路上より排除
2026-03-08 基板に反映
2026-03-11 配線のやり直しをやり直し
2026-03-17 Add schematics and boards information to README
    Added schematics and boards section with links to KiCAD resources.
2026-03-19 2.0に改版
2026-03-20 ERC/DRCを通す
2026-03-29 hc4.vリメイク版
2026-04-08 基板途中
2026-04-11 disasm関数のバッファ管理を改善し、命令の処理を修正
2026-04-19 feat:HC4e改版,BOMを令和最新版に更新,KiCadを10に更新
2026-04-19 feat: HC4eの新しいモジュールを追加し、ALUとメモリ操作を実装
2026-05-02 割り込み処理を修正、ver3基板に向けてマイコン設定を追加、veriloの誤りを修正
2026-05-04 nRD/WR制御とROMの制御を分離、AVR16EA48の設定を修正
2026-05-04 基板を若干改版、フットプリントの指定が外れていたのを修正
2026-05-23 自動配線前
2026-05-23 HC4eRev2完成
